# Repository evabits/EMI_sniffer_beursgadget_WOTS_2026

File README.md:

Here you will find the complete source documentation of the EMI sniffer after WOTS2026.

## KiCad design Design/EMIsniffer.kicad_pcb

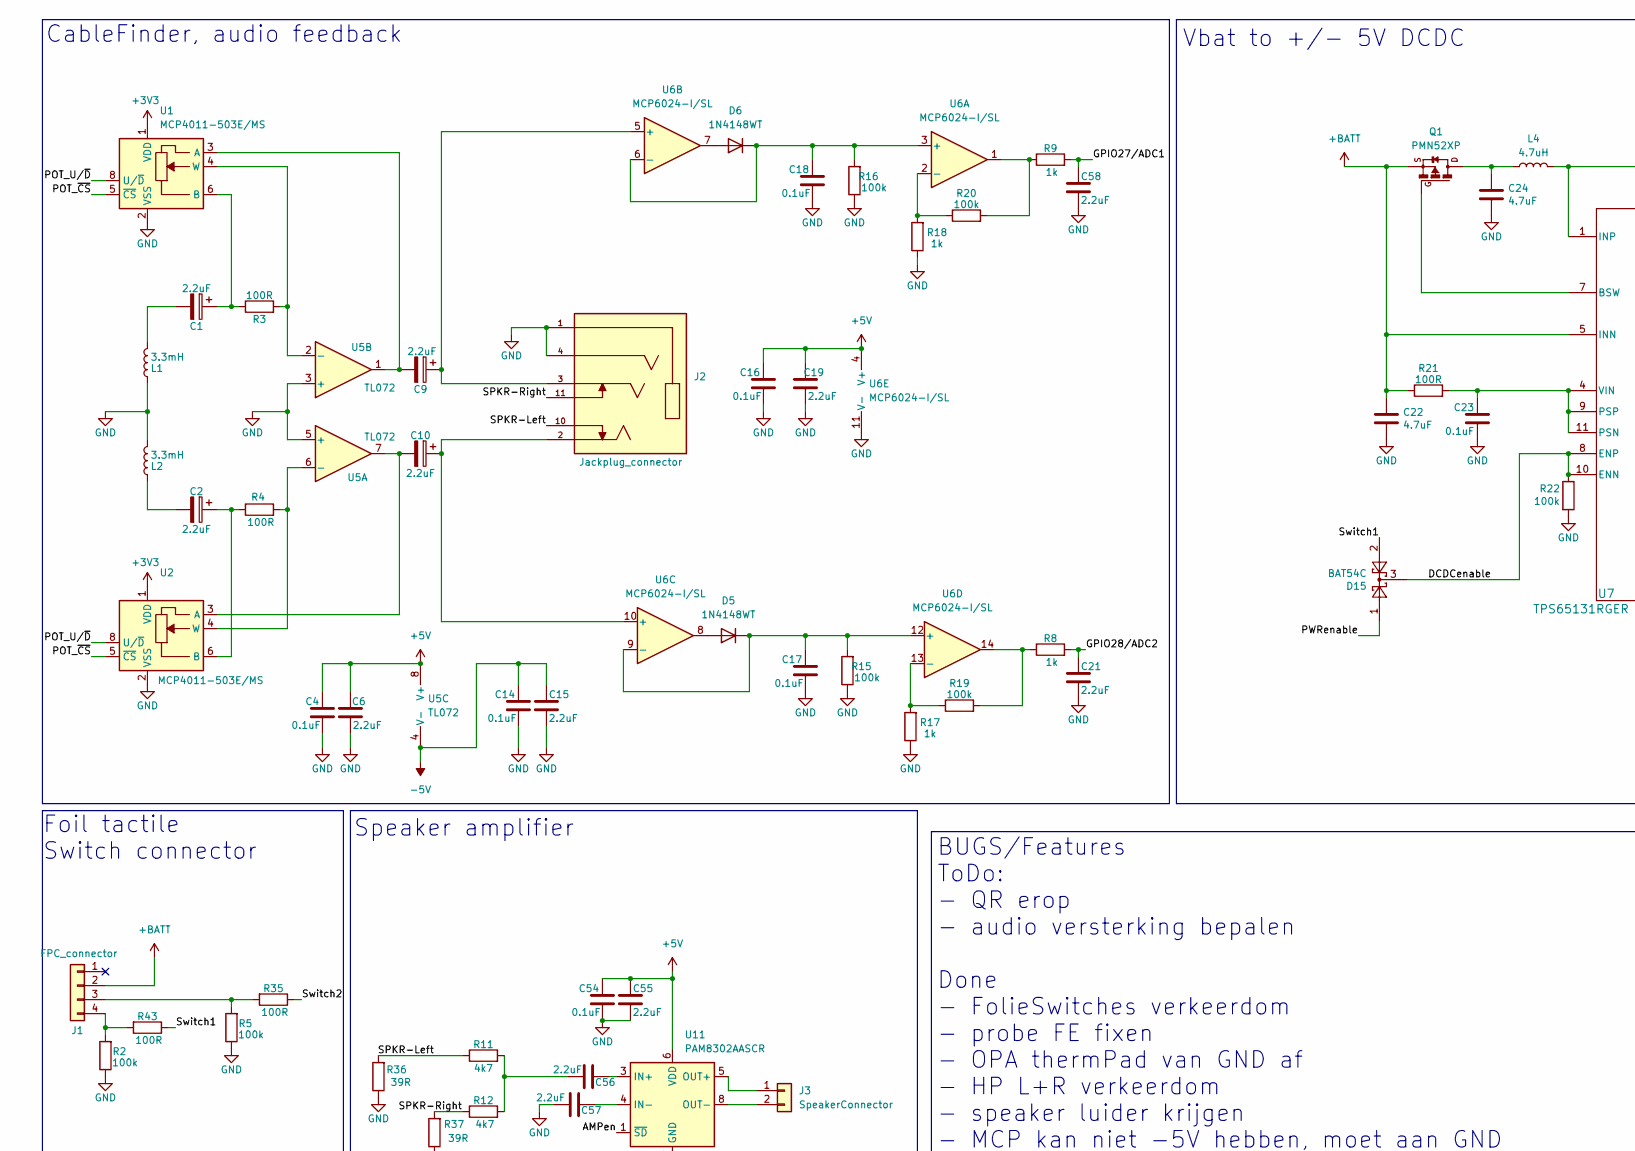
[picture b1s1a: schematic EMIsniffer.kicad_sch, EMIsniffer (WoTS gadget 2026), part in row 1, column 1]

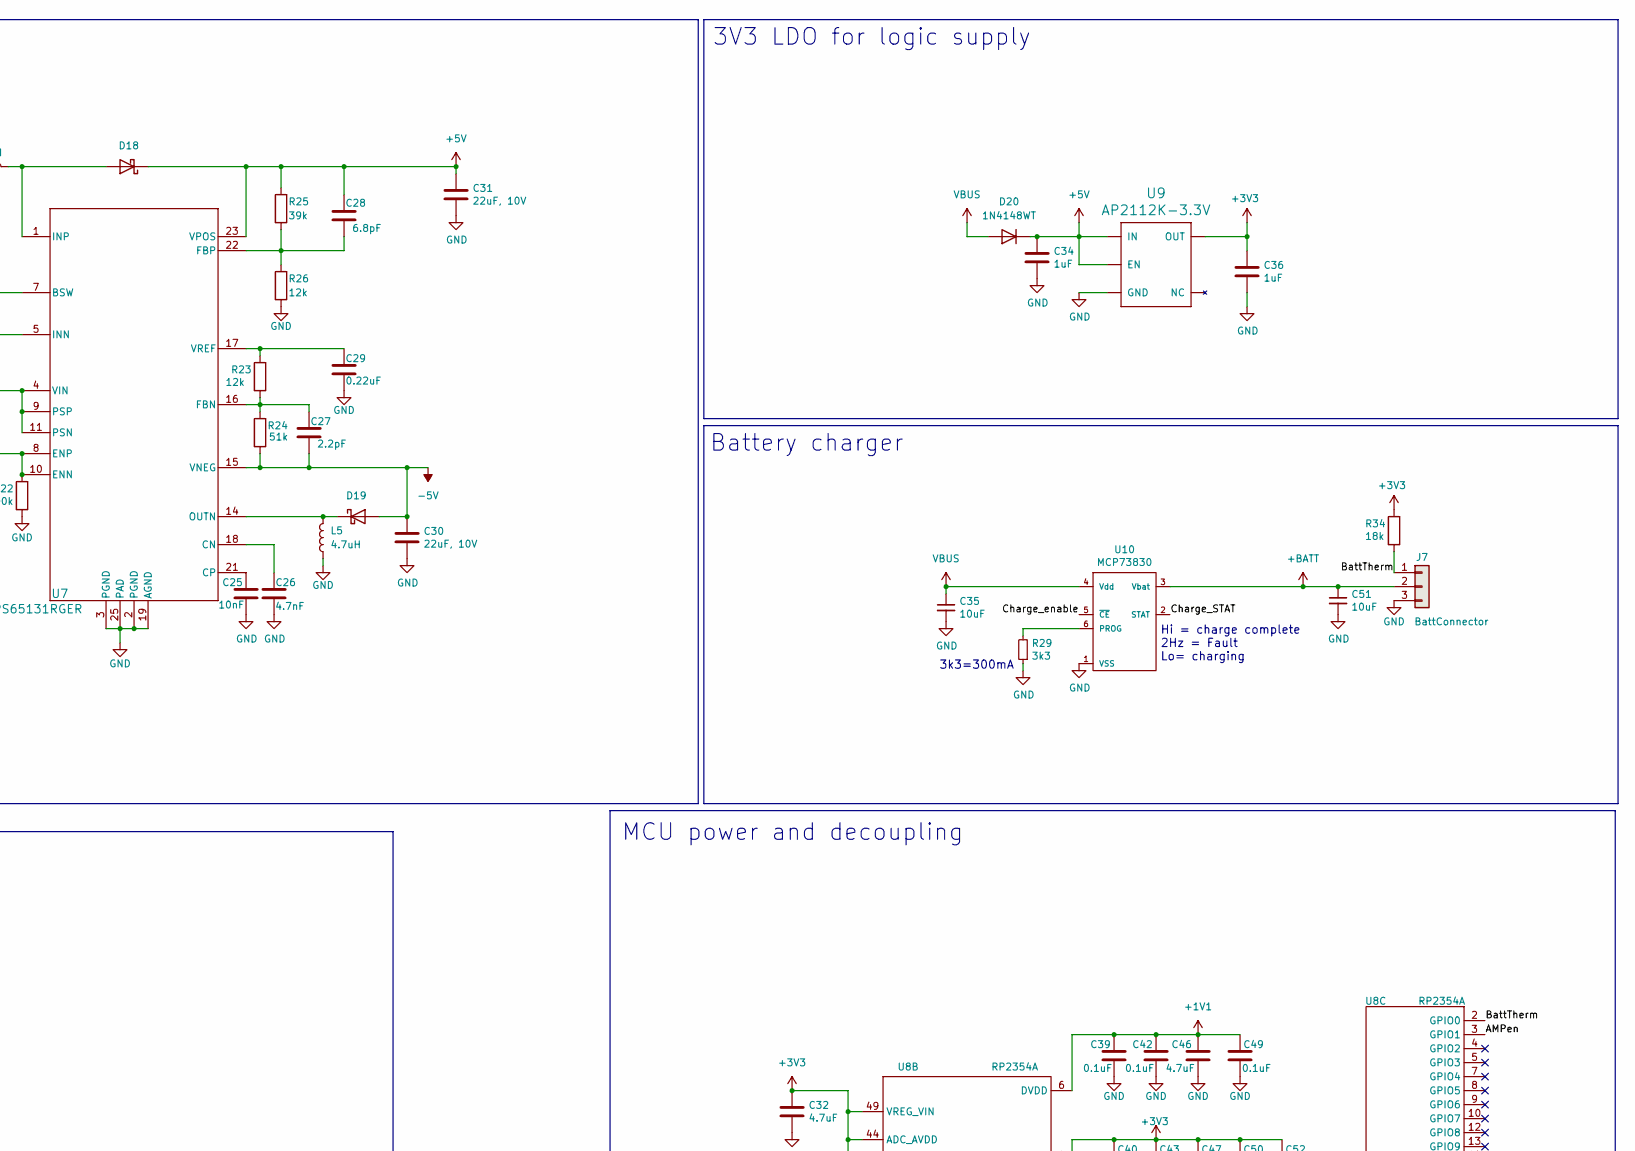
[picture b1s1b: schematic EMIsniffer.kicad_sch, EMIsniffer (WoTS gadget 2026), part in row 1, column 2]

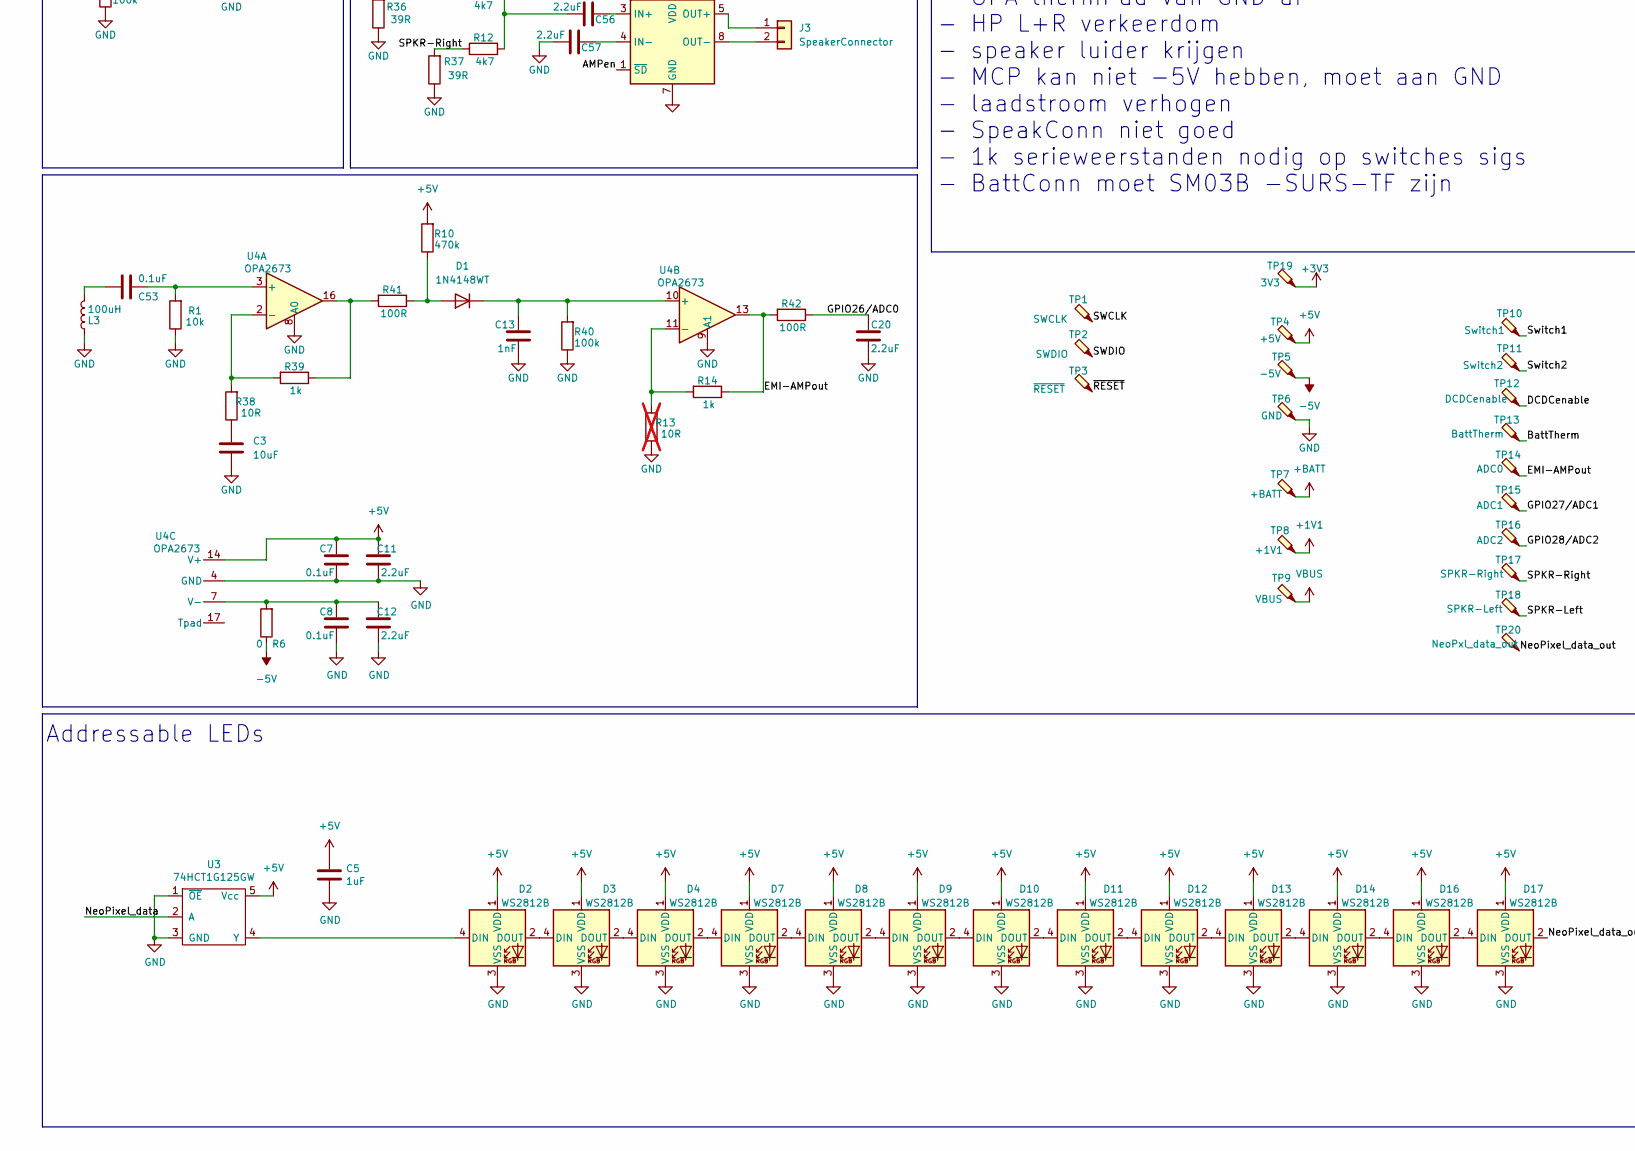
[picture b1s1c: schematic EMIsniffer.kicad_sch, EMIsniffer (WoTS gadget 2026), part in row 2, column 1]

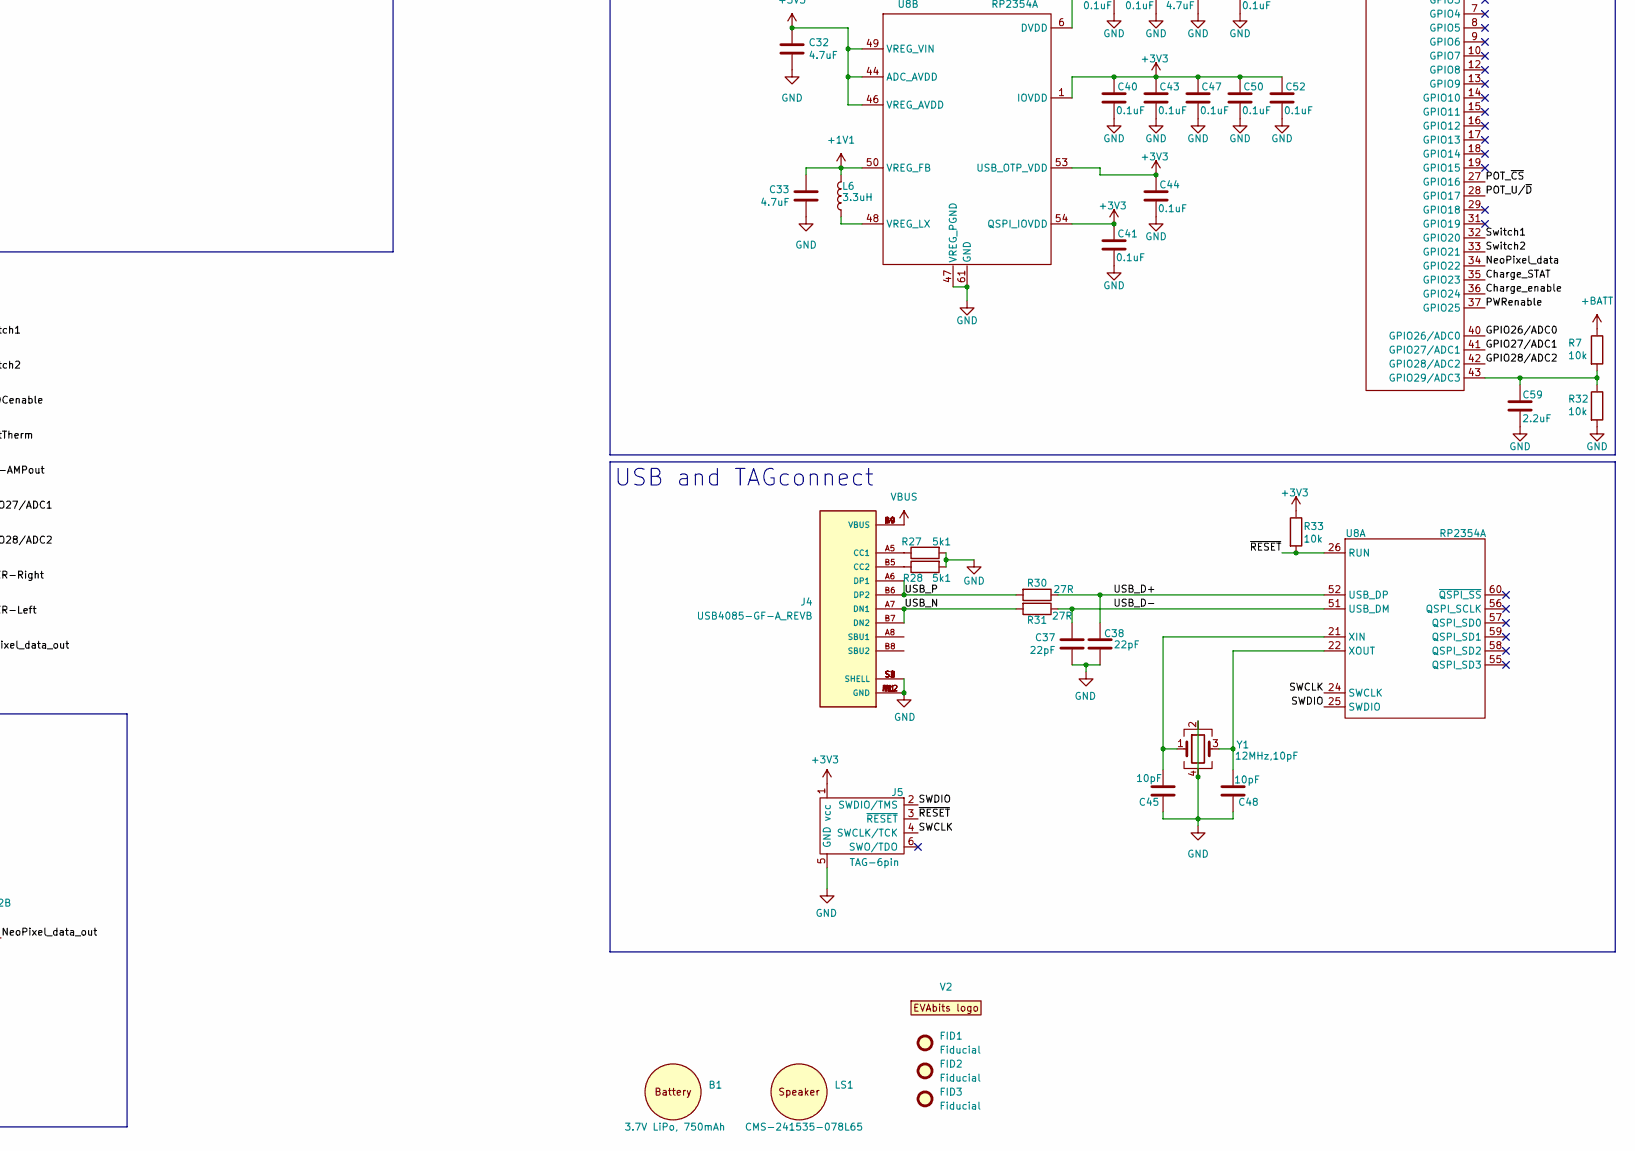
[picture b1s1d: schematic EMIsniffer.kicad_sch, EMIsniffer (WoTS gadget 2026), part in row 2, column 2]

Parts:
B1: 3.7V LiPo, 750mAh; place_marker; Partnumber DJ343650
C1, C2, C9, C10: 2.2uF; C_Elec_4x5.4; Partnumber 865090540001
C3, C35, C51: 10uF; C_0805_2012Metric
C4, C7, C8, C14, C16, C17, C18, C23, C39, C40, C41, C42, C43, C44, C47, C49, C50, C52, C53, C54: 0.1uF; C_0402_1005Metric
C5, C34, C36: 1uF; C_0603_1608Metric
C6, C11, C12, C15, C19, C20, C21, C55, C56, C57, C58, C59: 2.2uF; C_0603_1608Metric
C13: 1nF; C_0402_1005Metric
C22, C24, C32, C33, C46: 4.7uF; C_0603_1608Metric
C25: 10nF; C_0402_1005Metric
C26: 4.7nF; C_0402_1005Metric
C27: 2.2pF; C_0402_1005Metric
C28: 6.8pF; C_0402_1005Metric
C29: 0.22uF; C_0402_1005Metric
C30, C31: 22uF, 10V; C_1206_3216Metric
C37, C38: 22pF; C_0402_1005Metric
C45, C48: 10pF; C_0402_1005Metric
D1, D5, D6, D20: 1N4148WT; D_SOD-523; Partnumber 1N4148WT
D2, D3, D4, D7, D8, D9, D10, D11, D12, D13, D14, D16, D17: WS2812B; LED_WS2812B_PLCC4_5.0x5.0mm_P3.2mm; Partnumber 1315050930002
D15: BAT54C; SOT-23; Partnumber BAT54C
D18, D19: SK12; D_SMA; Partnumber SK12
FID1, FID2, FID3: Fiducial; Fiducial_1.5mm_Mask3mm
J1: FPC_connector; TE_84952-4_1x04-1MP_P1.0mm_Horizontal; Partnumber TE_84952-4
J2: Jackplug_connector; CUI_SJ2-35954D-SMT-TR; PARTREV 1.04
J3: SpeakerConnector; Molex_PicoBlade_53398-0271_1x02-1MP_P1.25mm_Vertical; Partnumber 0533980271
J4: USB4085-GF-A_REVB; GCT_USB4085-GF-A_REVB; PARTREV B
J5: TAG-6pin; Tag-Connect_TC2030-IDC-NL_2x03_P1.27mm_Vertical; Partnumber DNP
J7: BattConnector; JST_SUR_SM03B-SURS-TF_1x03-1MP_P0.80mm_Horizontal; Partnumber SM03B -SURS-TF
L1, L2: 3.3mH; L_Wurth_WE-TI-8095; Partnumber 7447720332
L3: 100uH; IND_LQH2HNH_03_MUR; Partnumber LQH2HNH101J03L
L4, L5: 4.7uH; L_Taiyo-Yuden_NR-40xx_HandSoldering; Partnumber NRS4018T4R7MDGJ
L6: 3.3uH; L_Wuerth_PMCI-201610; Partnumber AOTA-B201610S3R3-101-T
LS1: CMS-241535-078L65; place_marker; Partnumber CMS-241535-078L65
Q1: PMN52XP; TSOP-6_1.65x3.05mm_P0.95mm; Partnumber PMN52XP
R1, R7, R32, R33: 10k; R_0603_1608Metric
R2, R5, R15, R16, R19, R20, R22, R40: 100k; R_0603_1608Metric
R3, R4, R21, R35, R41, R42, R43: 100R; R_0603_1608Metric
R6: 0; R_0603_1608Metric
R8, R9, R14, R17, R18, R39: 1k; R_0603_1608Metric
R10: 470k; R_0603_1608Metric
R11, R12: 4k7; R_0603_1608Metric
R13: 10R; R_0603_1608Metric; not fitted
R23, R26: 12k; R_0603_1608Metric
R24: 51k; R_0603_1608Metric
R25: 39k; R_0603_1608Metric
R27, R28: 5k1; R_0603_1608Metric
R29: 3k3; R_0603_1608Metric
R30, R31: 27R; R_0603_1608Metric
R34: 18k; R_0603_1608Metric
R36, R37: 39R; R_0603_1608Metric
R38: 10R; R_0603_1608Metric
TP1: SWCLK; TestPoint_Pad_D1.5mm; Partnumber DNP
TP2: SWDIO; TestPoint_Pad_D1.5mm; Partnumber DNP
TP3: ~{RESET}; TestPoint_Pad_D1.5mm; Partnumber DNP
TP4: +5V; TestPoint_Pad_D1.5mm; Partnumber DNP
TP5: -5V; TestPoint_Pad_D1.5mm; Partnumber DNP
TP6: GND; TestPoint_Pad_D1.5mm; Partnumber DNP
TP7: +BATT; TestPoint_Pad_D1.5mm; Partnumber DNP
TP8: +1V1; TestPoint_Pad_D1.5mm; Partnumber DNP
TP9: VBUS; TestPoint_Pad_D1.5mm; Partnumber DNP
TP10: Switch1; TestPoint_Pad_D1.5mm; Partnumber DNP
TP11: Switch2; TestPoint_Pad_D1.5mm; Partnumber DNP
TP12: DCDCenable; TestPoint_Pad_D1.5mm; Partnumber DNP
TP13: BattTherm; TestPoint_Pad_D1.5mm; Partnumber DNP
TP14: ADC0; TestPoint_Pad_D1.5mm; Partnumber DNP
TP15: ADC1; TestPoint_Pad_D1.5mm; Partnumber DNP
TP16: ADC2; TestPoint_Pad_D1.5mm; Partnumber DNP
TP17: SPKR-Right; TestPoint_Pad_D1.5mm; Partnumber DNP
TP18: SPKR-Left; TestPoint_Pad_D1.5mm; Partnumber DNP
TP19: 3V3; TestPoint_Pad_D1.5mm; Partnumber DNP
TP20: NeoPxl_data_out; TestPoint_Pad_D1.5mm; Partnumber DNP
U1, U2: MCP4011-503E/MS; MSOP-8_3x3mm_P0.65mm; Partnumber MCP4011-503E/MS
U3: 74HCT1G125GW; SOT-353_SC-70-5; Partnumber 74HCT1G125GW
U4: OPA2673; QFN-16-1EP_4x4mm_P0.65mm_EP2.1x2.1mm; Partnumber OPA2673IRGVR
U5: TL072; SO-8_3.9x4.9mm_P1.27mm; Partnumber TL072
U6: MCP6024-I/SL; SOIC-14_3.9x8.7mm_P1.27mm; Partnumber MCP6024-I/SL
U7: TPS65131RGER; VQFN-24-1EP_4x4mm_P0.5mm_EP2.5x2.5mm; Partnumber TPS65131-Q1
U8: RP2354A; QFN-60-1EP_7x7mm_P0.4mm_EP3.4x3.4mm; Partnumber RP2354A
U9: AP2112K-3.3V; TSOT-23-5; Partnumber AP2112K-3.3
U10: MCP73830; DFN-6-1EP_2x2mm_P0.5mm_EP0.61x1.42mm; Partnumber MCP73830T-2AAI/MYY
U11: PAM8302AASCR; MSOP-8_3x3mm_P0.65mm; Partnumber PAM8302AASCR
V2: EVAbits_logo; EVAbits_newlogo 25x6mm
Y1: 12MHz,10pF; Crystal_SMD_3225-4Pin_3.2x2.5mm; Partnumber NX3225SA-12MHZ-STD-CSR-6

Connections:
+1V1: C33.2, C39.1, C42.1, C46.2, C49.1, L6.1, TP8.1, U8.6 (DVDD), U8.23 (DVDD), U8.39 (DVDD), U8.50 (VREG_FB)
+3V3: C32.2, C36.2, C40.1, C41.1, C43.1, C44.1, C47.1, C50.1, C52.1, J5.1 (vcc), R33.1, R34.1, TP19.1, U1.1 (VDD), U2.1 (VDD), U8.1 (IOVDD), U8.11 (IOVDD), U8.20 (IOVDD), U8.30 (IOVDD), U8.38 (IOVDD), U8.44 (ADC_AVDD), U8.45 (IOVDD), U8.46 (VREG_AVDD), U8.49 (VREG_VIN), U8.53 (USB_OTP_VDD), U8.54 (QSPI_IOVDD), U9.5 (OUT)
+5V: C4.1, C5.2, C6.2, C7.1, C11.2, C16.1, C19.2, C28.1, C31.2, C34.2, C54.1, C55.2, D2.1 (VDD), D3.1 (VDD), D4.1 (VDD), D7.1 (VDD), D8.1 (VDD), D9.1 (VDD), D10.1 (VDD), D11.1 (VDD), D12.1 (VDD), D13.1 (VDD), D14.1 (VDD), D16.1 (VDD), D17.1 (VDD), D18.1 (K), D20.1 (K), R10.2, R25.1, TP4.1, U3.5 (Vcc), U4.14 (V+), U5.8 (V+), U6.4 (V+), U7.23 (VPOS), U9.1 (IN), U9.3 (EN), U11.6 (VDD)
+BATT: C22.2, C51.1, J1.2, J7.2, Q1.4 (S), R7.1, R21.1, TP7.1, U7.5 (INN), U7.6 (INN), U10.3 (Vbat)
-5V: C14.1, C15.2, C27.2, C30.2, D19.2 (A), R6.1, R24.2, TP5.1, U5.4 (V-), U7.15 (VNEG)
/AMPen: U8.3 (GPIO1), U11.1 (~SD)
/BattTherm: J7.1, R34.2, TP13.1, U8.2 (GPIO0)
/Charge_STAT: U8.35 (GPIO23), U10.2 (STAT)
/Charge_enable: U8.36 (GPIO24), U10.5 (~CE)
/DCDCenable: D15.3, R22.1, TP12.1, U7.8 (ENP), U7.10 (ENN)
/EMI-AMPout: R14.1, R42.2, TP14.1, U4.13
/GPIO26/ADC0: C20.2, R42.1, U8.40 (GPIO26/ADC0)
/GPIO27/ADC1: C58.2, R9.2, TP15.1, U8.41 (GPIO27/ADC1)
/GPIO28/ADC2: C21.2, R8.2, TP16.1, U8.42 (GPIO28/ADC2)
/NeoPixel_data: U3.2 (A), U8.34 (GPIO22)
/NeoPixel_data_out: D17.2 (DOUT), TP20.1
/POT_U/~D: U1.8 (U/~D), U2.8 (U/~D), U8.28 (GPIO17)
/POT_~CS: U1.5 (~CS), U2.5 (~CS), U8.27 (GPIO16)
/PWRenable: D15.1, U8.37 (GPIO25)
/SPKR-Left: J2.10, R11.1, R36.2, TP18.1
/SPKR-Right: J2.11, R12.1, R37.2, TP17.1
/SWCLK: J5.4 (SWCLK/TCK), TP1.1, U8.24 (SWCLK)
/SWDIO: J5.2 (SWDIO/TMS), TP2.1, U8.25 (SWDIO)
/Switch1: D15.2, R43.1, TP10.1, U8.32 (GPIO20)
/Switch2: R35.1, TP11.1, U8.33 (GPIO21)
/USB_D+: C38.2, R30.1, U8.52 (USB_DP)
/USB_D-: C37.1, R31.1, U8.51 (USB_DM)
/USB_N: J4.A7 (DN1), J4.B7 (DN2), R31.2
/USB_P: J4.A6 (DP1), J4.B6 (DP2), R30.2
/~RESET: J5.3 (~RESET), R33.2, TP3.1, U8.26 (RUN)
GND: C3.2, C4.2, C5.1, C6.1, C7.2, C8.2, C11.1, C12.1, C13.2, C14.2, C15.1, C16.2, C17.2, C18.2, C19.1, C20.1, C21.1, C22.1, C23.2, C24.1, C25.2, C26.2, C29.2, C30.1, C31.1, C32.1, C33.1, C34.1, C35.2, C36.1, C37.2, C38.1, C39.2, C40.2, C41.2, C42.2, C43.2, C44.2, C45.2, C46.1, C47.2, C48.1, C49.2, C50.2, C51.2, C52.2, C54.2, C55.1, C57.2, C58.1, C59.1, D2.3 (VSS), D3.3 (VSS), D4.3 (VSS), D7.3 (VSS), D8.3 (VSS), D9.3 (VSS), D10.3 (VSS), D11.3 (VSS), D12.3 (VSS), D13.3 (VSS), D14.3 (VSS), D16.3 (VSS), D17.3 (VSS), J2.1, J2.4, J4.A1 (GND), J4.A12 (GND), J4.B1 (GND), J4.B12 (GND), J4.S1 (SHELL), J4.S2 (SHELL), J4.S3 (SHELL), J4.S4 (SHELL), J5.5 (GND), J7.3, L1.1, L2.2, L3.1, L5.1, R1.1, R2.1, R5.1, R13.1, R15.1, R16.1, R17.1, R18.1, R22.2, R26.2, R27.2, R28.2, R29.1, R32.2, R36.1, R37.1, R40.1, TP6.1, U1.2 (VSS), U2.2 (VSS), U3.1 (~OE), U3.3 (GND), U4.1 (GND), U4.4 (GND), U4.5 (GND), U4.6 (GND), U4.8 (A0), U4.9 (A1), U4.12 (GND), U4.15 (GND), U5.3 (+), U5.5 (+), U6.11 (V-), U7.2 (PGND), U7.3 (PGND), U7.19 (AGND), U7.25 (PAD), U8.47 (VREG_PGND), U8.61 (GND), U9.2 (GND), U10.1 (VSS), U10.7 (VSS), U11.7 (GND), Y1.2, Y1.4
INP: D18.2 (A), L4.2, U7.1 (INP), U7.24 (INP)
unnamed: C1.2, L1.2
unnamed: C2.2, L2.1
unnamed: C3.1, R38.1
unnamed: C24.2, L4.1, Q1.1 (D), Q1.2 (D), Q1.5 (D), Q1.6 (D)
unnamed: C53.1, L3.2
unnamed: C56.2, R11.2, R12.2
unnamed: D1.2 (A), R10.1, R41.1
unnamed: C13.1, D1.1 (K), R40.2, U4.10 (+)
unnamed: D2.4 (DIN), U3.4 (Y)
unnamed: D2.2 (DOUT), D3.4 (DIN)
unnamed: D3.2 (DOUT), D4.4 (DIN)
unnamed: D4.2 (DOUT), D7.4 (DIN)
unnamed: D5.2 (A), U6.8
unnamed: C17.1, D5.1 (K), R15.2, U6.9 (-), U6.12 (+)
unnamed: D6.2 (A), U6.7
unnamed: C18.1, D6.1 (K), R16.2, U6.3 (+), U6.6 (-)
unnamed: D7.2 (DOUT), D8.4 (DIN)
unnamed: D8.2 (DOUT), D9.4 (DIN)
unnamed: D9.2 (DOUT), D10.4 (DIN)
unnamed: D10.2 (DOUT), D11.4 (DIN)
unnamed: D11.2 (DOUT), D12.4 (DIN)
unnamed: D12.2 (DOUT), D13.4 (DIN)
unnamed: D13.2 (DOUT), D14.4 (DIN)
unnamed: D14.2 (DOUT), D16.4 (DIN)
unnamed: D16.2 (DOUT), D17.4 (DIN)
unnamed: J1.3, R5.2, R35.2
unnamed: J1.4, R2.2, R43.2
unnamed: J3.1, U11.5 (OUT+)
unnamed: J3.2, U11.8 (OUT-)
unnamed: J4.A5 (CC1), R27.1
unnamed: J4.B5 (CC2), R28.1
unnamed: Q1.3 (G), U7.7 (BSW)
unnamed: R8.1, R19.2, U6.14
unnamed: R9.1, R20.2, U6.1
unnamed: R39.1, R41.2, U4.16
unnamed: C9.2, U1.3 (A), U5.1
unnamed: C1.1, R3.1, U1.6 (B)
unnamed: R3.2, U1.4 (W), U5.2 (-)
unnamed: C10.2, U2.3 (A), U5.7
unnamed: C2.1, R4.1, U2.6 (B)
unnamed: R4.2, U2.4 (W), U5.6 (-)
unnamed: C53.2, R1.2, U4.3 (+)
unnamed: R38.2, R39.2, U4.2 (-)
unnamed: R13.2, R14.2, U4.11 (-)
unnamed: C8.1, C12.2, R6.2, U4.7 (V-)
unnamed: R18.2, R20.1, U6.2 (-)
unnamed: C9.1, J2.3, U6.5 (+)
unnamed: C10.1, J2.2, U6.10 (+)
unnamed: R17.2, R19.1, U6.13 (-)
unnamed: C26.1, U7.18 (CN)
unnamed: C25.1, U7.21 (CP)
unnamed: C27.1, R23.2, R24.1, U7.16 (FBN)
unnamed: C28.2, R25.2, R26.1, U7.22 (FBP)
unnamed: C23.1, R21.2, U7.4 (VIN), U7.9 (PSP), U7.11 (PSN)
unnamed: C29.1, R23.1, U7.17 (VREF)
unnamed: C45.1, U8.21 (XIN), Y1.1
unnamed: C48.2, U8.22 (XOUT), Y1.3
unnamed: L6.2, U8.48 (VREG_LX)
unnamed: C59.2, R7.2, R32.1, U8.43 (GPIO29/ADC3)
unnamed: R29.2, U10.6 (PROG)
unnamed: C56.1, U11.3 (IN+)
unnamed: C57.1, U11.4 (IN-)
OUTN: D19.1 (K), L5.2, U7.13 (OUTN), U7.14 (OUTN)
VBUS: C35.1, D20.2 (A), J4.A4 (VBUS), J4.A9 (VBUS), J4.B4 (VBUS), J4.B9 (VBUS), TP9.1, U10.4 (Vdd)

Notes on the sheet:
Speaker amplifier
3k3=300mA
USB and TAGconnect
Hi = charge complete 2Hz = Fault Lo= charging
MCU power and decoupling
CableFinder, audio feedback
3V3 LDO for logic supply
Addressable LEDs
Vbat to +/- 5V DCDC
Foil tactile Switch connector
Battery charger
BUGS/Features ToDo: - QR erop - audio versterking bepalen Done - FolieSwitches verkeerdom - probe FE fixen - OPA thermPad van GND af - HP L+R verkeerdom - speaker luider krijgen - MCP kan niet -5V hebben, moet aan GND - laadstroom verhogen - SpeakConn niet goed - 1k serieweerstanden nodig op switch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

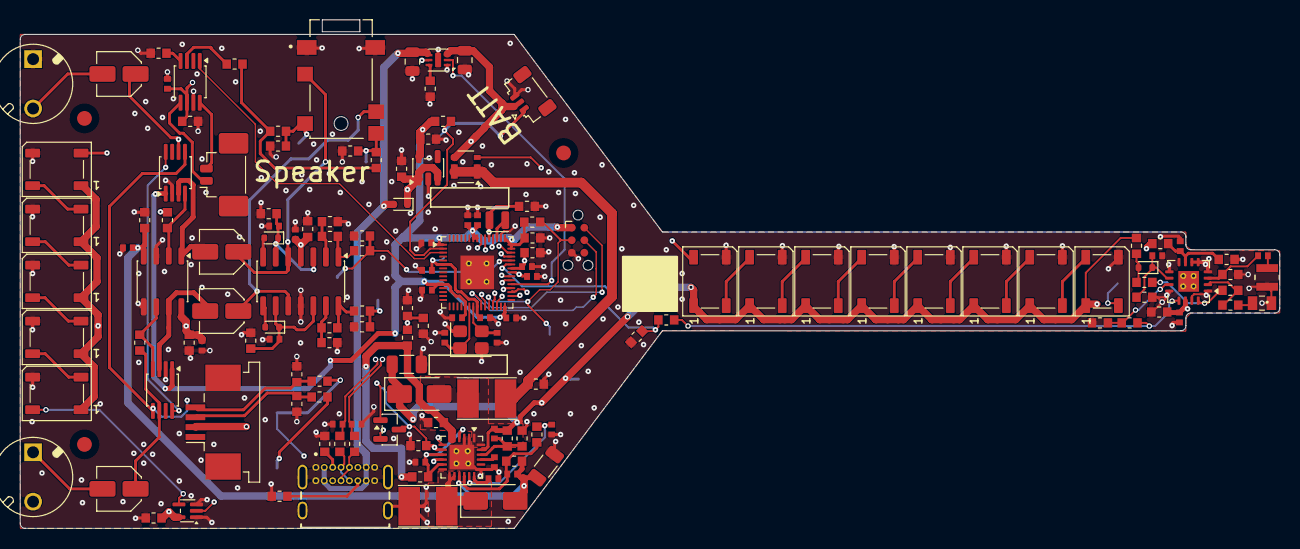
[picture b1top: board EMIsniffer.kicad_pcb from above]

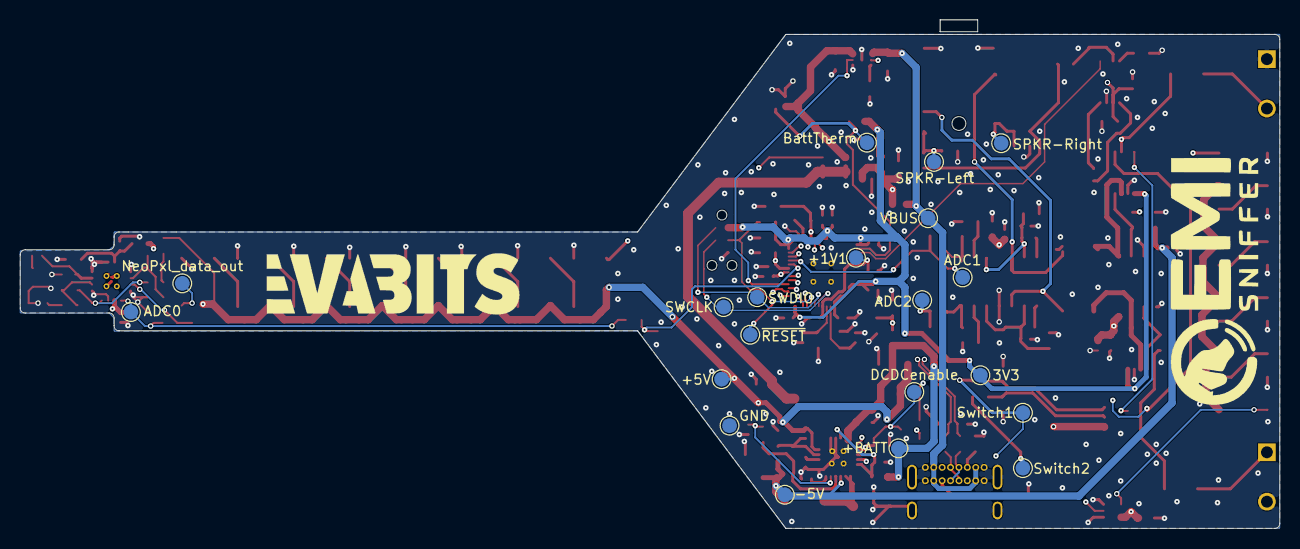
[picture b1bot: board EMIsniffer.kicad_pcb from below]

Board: 4 copper layers, 127.5 x 51.5 mm, 173 parts (22 on the bottom side), 96 nets.

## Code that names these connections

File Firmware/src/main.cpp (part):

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#include <hardware/structs/pads_bank0.h>

// --- Hardware ---------------------------------------------------------------
static constexpr uint8_t  LED_PIN   = 22;   // WS2812 data line (GPIO22)
static constexpr uint16_t LED_COUNT = 13;   // visible string: LED 1 through 13
static constexpr uint16_t LED_CHAIN = LED_COUNT + 1;  // +1 extra: test DOUT of LED 13
static constexpr uint8_t  ADC_PIN   = A0;   // ADC0 = GPIO26 -> VU meter (LED 6..13)
static constexpr uint8_t  ADC1_PIN  = A1;   // ADC1 = GPIO27 -> balance
static constexpr uint8_t  ADC2_PIN  = A2;   // ADC2 = GPIO28 -> balance

// --- Buttons -----------------------------------------------------------------
static constexpr uint8_t  POWER_HOLD_PIN       = 25;   // load-switch latch: HIGH = power on
static constexpr uint8_t  BUTTON_PIN           = 20;   // power button AND volume + (GPIO20)
static constexpr bool     BUTTON_ACTIVE_HIGH   = true;  // pressed = GPIO20 HIGH
static constexpr uint32_t POWER_OFF_HOLD_MS    = 2000;  // hold 2s -> power off
static constexpr uint8_t  VOL_DOWN_PIN         = 21;   // 2nd button = volume - (GPIO21)
static constexpr bool     VOL_DOWN_ACTIVE_HIGH = true;  // assumption; flip if needed
static constexpr uint32_t CENTER_HOLD_MS       = 2000;  // hold volume - 2s -> centre the balance

// --- Battery (1-cell Li-Po) --------------------------------------------------
static constexpr uint8_t  VBAT_ADC_PIN       = A3;   // ADC3 = GPIO29, Vbat via 10k+10k divider
static constexpr uint8_t  CHARGE_STAT_PIN    = 23;   // MCP73830 STAT: LOW = charging
static constexpr float    ADC_VREF           = 3.3f; // ADC reference (VREF pin)
static constexpr float    VBAT_DIVIDER       = 2.0f; // 10k+10k -> ADC3 reads Vbat/2
// Vbat calibration factor lives in calibration.txt as vbat_cal (default in config.hpp).
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static constexpr uint8_t  AMP_EN_PIN         = 1;    // HIGH = amp on; LOW while charging

// --- MCP4011 digital pot (increment/decrement interface) ---------------------
static constexpr uint8_t  POT_CS_PIN         = 16;   // ChipSelect (active-low)
static constexpr uint8_t  POT_UD_PIN         = 17;   // Up/Down (direction + step pulse)
static constexpr uint8_t  POT_TAPS           = 64;   // MCP4011: 64 wiper positions (0..63)

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};
static Calibration cal;
static bool stQuiet = false;   // after ST: START: no unsolicited serial
enum class DiagMode : uint8_t { None, PinTest, Sweep, Gpio29, Adc };
static DiagMode diagMode = DiagMode::None;
enum class LoopMode : uint8_t { Diag, Quiet, ShowVolume, ShowBattery, Emi };

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
static bool readCharging() {
  if constexpr (Features::ignoreCharging) return false;
  return digitalRead(CHARGE_STAT_PIN) == LOW;
}

// Mute the amp while charging (EN low); enable it on battery (EN high).
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static constexpr uint32_t VOL_DISPLAY_MS = 1200;  // how long to show after a change

static void potBegin() {
  pinMode(POT_CS_PIN, OUTPUT);
  digitalWrite(POT_CS_PIN, HIGH);   // deselected
  pinMode(POT_UD_PIN, OUTPUT);
  digitalWrite(POT_UD_PIN, HIGH);
}
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static void potMove(bool up, uint8_t steps) {
  digitalWrite(POT_UD_PIN, up ? HIGH : LOW);   // set direction first
  delayMicroseconds(5);
  digitalWrite(POT_CS_PIN, LOW);               // select
  delayMicroseconds(5);
  for (uint8_t i = 0; i < steps; i++) {
    digitalWrite(POT_UD_PIN, up ? LOW : HIGH); // opposite edge
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    digitalWrite(POT_UD_PIN, up ? HIGH : LOW); // this edge = 1 step
    delayMicroseconds(5);
  }
  digitalWrite(POT_CS_PIN, HIGH);              // deselect
  delayMicroseconds(5);
}

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// ----------------------------------------------------------------------------
void setup() {
  // FIRST: take over the power latch so the power button can be released.
  // GPIO25 HIGH holds the load switch on; GPIO20 reads the button.
  pinMode(POWER_HOLD_PIN, OUTPUT);
  digitalWrite(POWER_HOLD_PIN, HIGH);
  pinMode(BUTTON_PIN, BUTTON_ACTIVE_HIGH ? INPUT_PULLDOWN : INPUT_PULLUP);
  pinMode(VOL_DOWN_PIN, VOL_DOWN_ACTIVE_HIGH ? INPUT_PULLDOWN : INPUT_PULLUP);  // volume -
  pinMode(CHARGE_STAT_PIN, INPUT_PULLUP);   // MCP73830 STAT (LOW = charging)

  pinMode(AMP_EN_PIN, OUTPUT);
  updateAmpEnable(readCharging());
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  setupFilesystem();
}

// Power the unit off: LEDs off and release the load switch (GPIO25). Power
// drops once the button is released (until then the button itself still
// holds the rail); on battery with no button held it drops immediately.
static void powerOff() {
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  while (true) { /* wait until the supply collapses */ }
}

// GPIO20 has a dual function:
//  - SHORT press (release < 2s) = volume + (pot 1 step up)
//  - hold 2s = power off
// Detection is only armed after the boot press is released
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  wasPressed = pressed;
}

// Watch the volume-down button (GPIO21): each press edge = pot 1 step down.
// Trimmed mean of 9 ADC samples: sort, drop the 2 lowest + 2 highest, average
// the middle 5. Kills single-sample outliers (RP2350 ADC DNL steps, LED-current
// transients on the 3V3 rail) that a plain average would drag along.
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static void diagPinTest() {
  static bool s = false;
  s = !s;
  digitalWrite(POT_CS_PIN, s ? HIGH : LOW);
  digitalWrite(POT_UD_PIN, s ? LOW  : HIGH);
  Serial.printf("PINTEST CS(16)=%d  UD(17)=%d\n", s ? 1 : 0, s ? 0 : 1);
  delay(1000);
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  const bool ie  = pad & PADS_BANK0_GPIO0_IE_BITS;
  const bool od  = pad & PADS_BANK0_GPIO0_OD_BITS;
  const int  a3  = adcSettledRead(A3);
  const bool charging = digitalRead(CHARGE_STAT_PIN) == LOW;
  Serial.printf("GPIO29 func=%lu OE=%lu OUT=%lu PUE=%d PDE=%d IE=%d OD=%d | A3=%4d | %s\n",
                (unsigned long)func, (unsigned long)oe, (unsigned long)out,
                pue, pde, ie, od, a3, charging ? "CHARGING" : "not");
  delay(200);
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  switch (diagMode) {
    case DiagMode::PinTest: diagPinTest(); return true;
    case DiagMode::Sweep:   diagPotSweep(); return true;
    case DiagMode::Gpio29:  diagGpio29(); return true;
    case DiagMode::Adc:     diagAdc(); return true;
    case DiagMode::None:    return false;
  }
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//   BATT      -> Vbat as integer millivolts
//   TAP=n     -> MCP4011 wiper tap, 0..63 (raw; 0 = loudest)
//   ADC=ALL   -> ADC: {ADC0}, {ADC1}, {ADC2}
//   ADC=0     -> ADC0 (GPIO26), 12-bit 0..4095; same for ADC=1 and ADC=2
//   LED=r,g,b -> all 13 LEDs + 1 extra (DOUT test) that colour; reply LED: OK
//   PINTEST   -> toggle pot CS/UD ~1 Hz (multimeter)
//   SWEEP     -> digital pot back and forth
//   GPIO29    -> live pad config of ADC3 + charge status
//   ADCDBG    -> A0..A3 + chip temp, continuous
static void pollSerialCommands() {
  static char buf[32];
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      } else if (strcmp(buf, "SWEEP") == 0) {
        diagMode = DiagMode::Sweep;
        Serial.print("SWEEP: OK\n");
      } else if (strcmp(buf, "GPIO29") == 0) {
        diagMode = DiagMode::Gpio29;
        Serial.print("GPIO29: OK\n");
      } else if (strcmp(buf, "ADCDBG") == 0) {
        diagMode = DiagMode::Adc;
        Serial.print("ADCDBG: OK\n");
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    Serial.printf("ADC0=%4u ema=%4d level=%u/%u | ADC1=%4u ADC2=%4u bal=%.2f LED%u | Vbat=%.2f chg=%d | (min=%u max=%u sm=%u)%s\n",
                  adc, (int)emaAdc, shown, VU_SEGMENTS,
                  a1, a2, emaBal, balLed + 1,
                  vbat, digitalRead(CHARGE_STAT_PIN) == LOW,
                  cal.adcMin, cal.adcMax, cal.smoothing,
                  driveConnected ? "  [disk mounted]" : "");
  }
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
